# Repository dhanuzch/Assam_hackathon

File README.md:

# Innovate for Assam

## Project Explanation Video
[Click here](http://www.youtube.com/watch?v=9En175bcu2Y).

## Project instructions and explanation document
This contains all the details to replicate this project, explanation and detailed instructions.
[Click here](/Assam_hack_report.pdf).
<br>
[Drive link](https://drive.google.com/file/d/1i1HEC_GRwBN9hoXFHEckwQVBD2L8Wx2i/view?usp=sharing).

## Project Working
#### 1_smart_vehicle_tracker
[Click here](Project_Images/1_website.gif)

## Folder Structure

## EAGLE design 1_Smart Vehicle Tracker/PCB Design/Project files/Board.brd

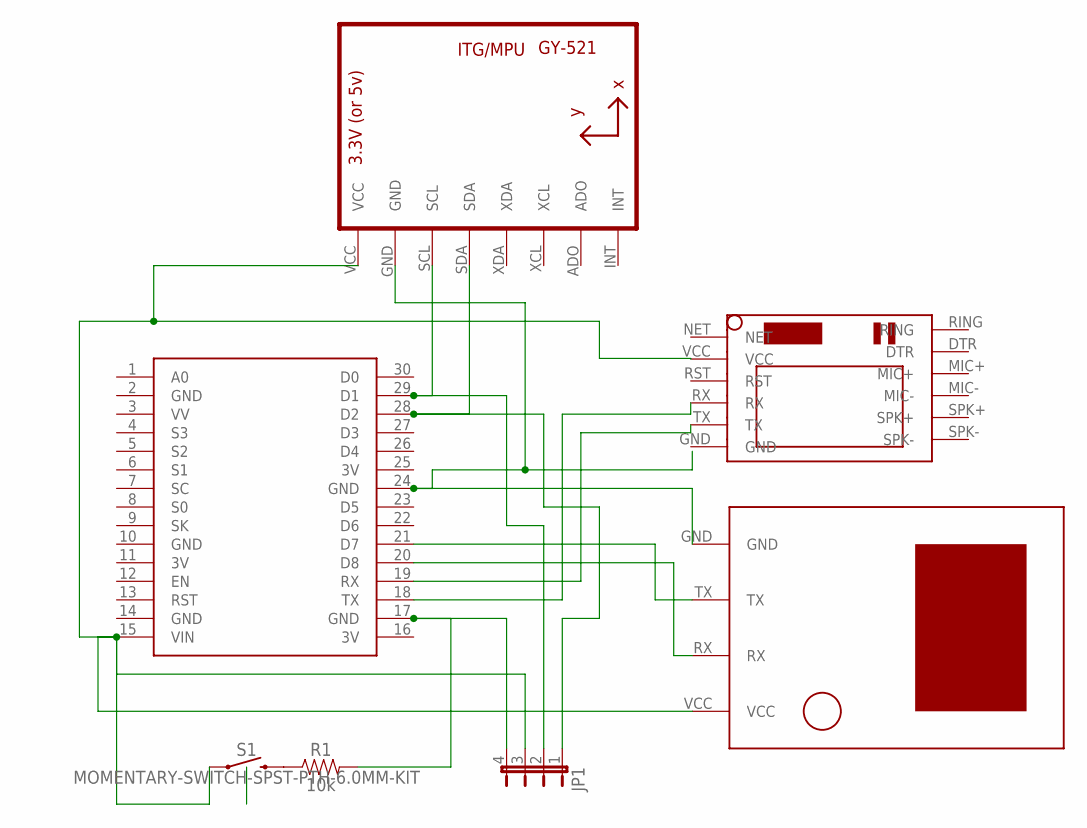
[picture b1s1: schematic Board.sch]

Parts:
JP1: JP4E; JP4
R1: 10k; AXIAL-0.3
S1: MOMENTARY-SWITCH-SPST-PTH-6.0MM-KIT; TACTILE_SWITCH_PTH_6.0MM_KIT
U1: GY-521MPU6050; GY-521
U$1: NODEMCU
U$2: SIM800LMODULE
U$3: U-BLOX-NEO6V2

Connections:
3V: U$1.11 (3V), U$1.16 (3V), U$1.25 (3V)
GND: U$1.2 (GND), U$1.10 (GND), U$1.14 (GND)
unnamed: U$1.21 (D7), U$3.TX
unnamed: U$1.20 (D8), U$3.RX
unnamed: U$1.19 (RX), U$2.TX
unnamed: U$1.18 (TX), U$2.RX
unnamed: U1.GND, U$1.24 (GND), U$3.GND
unnamed: JP1.3, S1.1, U1.VCC, U$1.15 (VIN), U$2.VCC, U$3.VCC
unnamed: JP1.2, U1.SCL, U$1.29 (D1)
unnamed: JP1.1, U1.SDA, U$1.28 (D2)
unnamed: R1.P$1 (1), S1.3 (2)
unnamed: JP1.4, R1.P$2 (2), U$1.17 (GND)

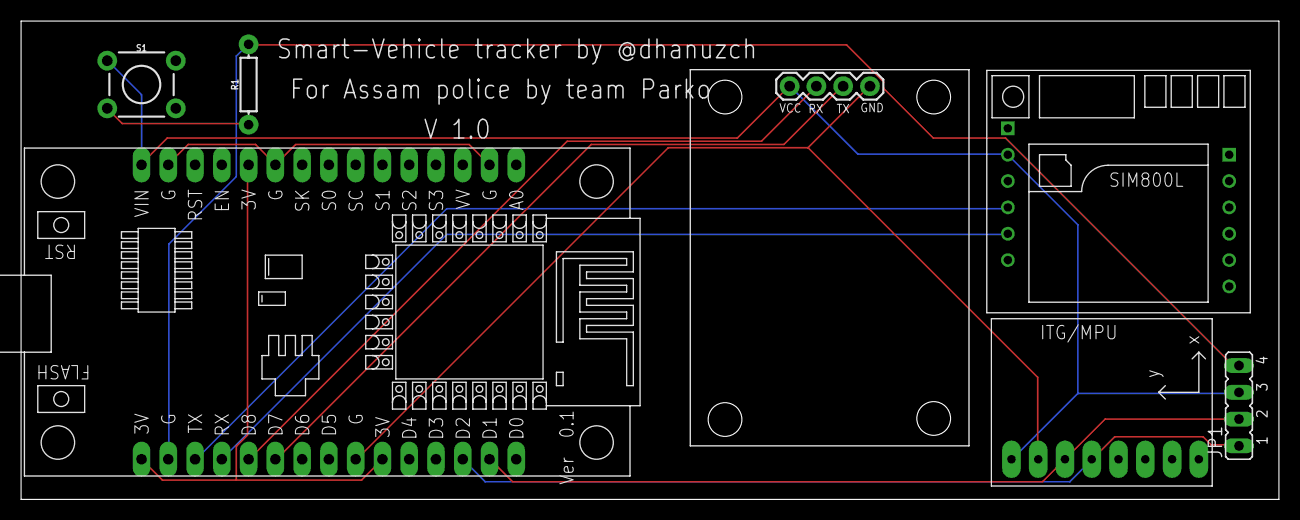
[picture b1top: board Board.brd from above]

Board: 2 copper layers, 119.4 x 45.4 mm, 7 parts (0 on the bottom side), 12 nets.

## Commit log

2020-09-23 second commit
2020-09-24 Third Commit
2020-09-27 fourth commit
2020-09-28 fifth commit
2020-09-30 seventh commit
2020-09-30 Eighth commit
2020-09-30 added photos
2020-09-30 Folder structure
2020-09-30 ninth commit
2020-09-30 tenth commit

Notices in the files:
parts and their libraries:
SparkFun-Resistors: Licensing: Creative Commons ShareAlike 4.0 International - https://creativecommons.org/licenses/by-sa/4.0
